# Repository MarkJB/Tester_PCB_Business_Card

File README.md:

# Tester PCB Business Card

A PCB Business Card designed by a tester, for testers (QA Engineers)

I've always liked the PCB business cards I've seen people design. They often have an interesting story about the why and the how, and sometimes even lead to a job offer as a result!

> Note: For any recruiters or prospective employers who end up here, I'm a software tester specializing in WebUI test automation. Electronics and hardware is a hobby (and occasionally a freelance gig in the Creative Technologist/Arts and Technology space)

I wanted to give it a go but couldn't think of anything compelling that was related to my primary industry (QA, Software Testing & Test Automation). Then I saw a recent [pong example on Hackaday](https://hackaday.com/2025/08/13/pcb-business-card-plays-pong-attracts-employer/) which made me wonder whether the author had done much testing, and that sparked the idea of creating a PCB business card all about testing.

There are 5 'test cases'\*, each one designed to be a little bit harder than the previous one and to focus on a different class of test. The hardware is somewhat limited, so how well each of the tests achieves its intended goal or how true it is to its test type is open for debate and I welcome feedback from actual testers!

The idea is that a tester should be able to look at the test case description, its test type and, given the available inputs and output, figure out how to get the tests to pass, treating it as a sort of black-box exploratory test session. Think of it as a fidget toy for tester.

That all said, I've not yet had any feedback from any testers so I don't know if its too easy or too hard. If you want to cheat, dig into this repo and you'll find the test case BDD scenarios and solutions (which I have deliberately not linked from any of the main READMEs), or as an alternative you can read the code (either the main firmware or the simulator should provide a white-box experience).

\* I use the term "test cases" to refer to the tests that the hardware is presenting to the end user to 'execute', but in some places I have also created actual tests for the code as well (like the Playwright tests for the simulator).

> Note: There may be minor differences between the simulator and the actual hardware due to implementation details or I changed direction while working on the firmware and haven't gotten round to updating the simulator.

So here is Rev A:

This is based on the CH32V003F4U6. A 27¢ micro controller with a one-wire programmer that costs less than $8. I had no experience with this when I started this project, but cost was a big factor with the card. I'm aiming for sub $2 per unit so I can a) afford to get a handful made and b) give them away at conferences and networking events.

> Note: I added a slot for attaching to a lanyard as I intend to give these out at networking and conference events.

This repo includes:

# Hardware

The [schematic](./resources/schematic.pdf), PCB design, BoM and JLCPCB ready production files [Kicad 9 files here](./hardware/)

# Software

## Simulator

Simulator [README](./software/simulator)

The simulator is built, tested and (if successful) deployed to GitHub pages by a [GitHub Actions pipeline](https://github.com/MarkJB/Tester_PCB_Business_Card/actions)

You can play with the deployed simulator here: [Simulator Demo](https://markjb.github.io/Tester_PCB_Business_Card/)

## Firmware

Uses platformio and the ch32fun framework.

[Main firmware](./software/firmware/tester_runtime/): The main firmware containing tests, test case runner, LED control, button functions etc.

[Board check](./software/firmware/board_check/): Simple test firmware to confirm LEDs and buttons are connected and working. Mainly used for testing hand assembled prototype boards.

[LED Tune](./software/firmware/led_tune/): Simple firmware to allow manual tuning of resistor values. shouldn't need this again unless the LEDs are changed for ones that are significantly different.

# Licenses

Copyright Mark Benson 2025

The hardware is licensed under the CERN-OHL-S v2 license.
The software is licensed under the MIT license.

Usual disclaimer - No warranty implied or given for any use or outcome of any of the available materials, etc. 

This isn't a toy, it's not suitable for children. As it's not in a case, there is a risk of short circuiting the components and battery, resulting in damage or overheating, so do not put it in your pocket or bag or anywhere where metal objects could cause short circuit. Note: Battery should be inserted + side up. Incorrectly inserted battery will short out resulting in damage or overheating. Use at your own risk.

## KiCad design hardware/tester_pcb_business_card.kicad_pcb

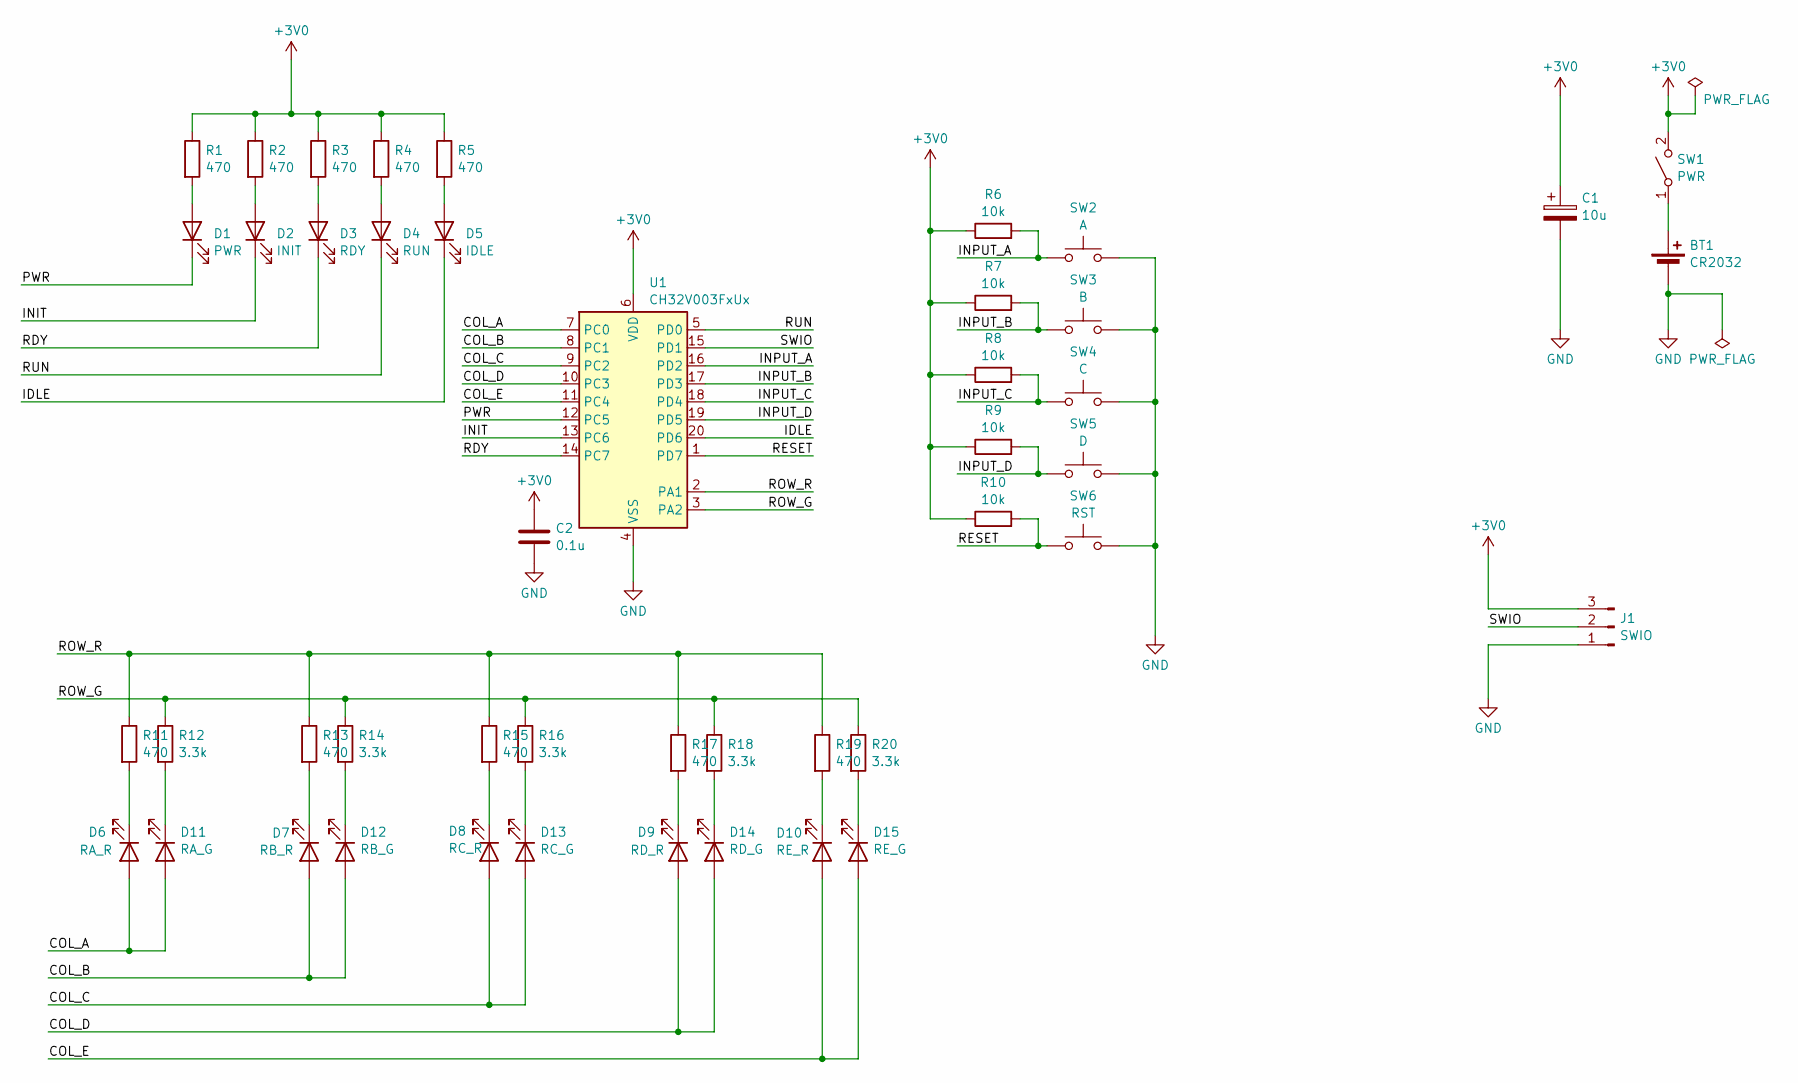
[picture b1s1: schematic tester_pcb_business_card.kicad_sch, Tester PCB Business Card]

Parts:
BT1: CR2032; MY-2032-12; LCSC C964833
C1: 10u; CP_EIA-3216-18_Kemet-A; LCSC C7171
C2: 0.1u; C_0805_2012Metric; LCSC C49678
D1: PWR; LED_0805_2012Metric; LCSC C84256
D2: INIT; LED_0805_2012Metric; LCSC C84256
D3: RDY; LED_0805_2012Metric; LCSC C84256
D4: RUN; LED_0805_2012Metric; LCSC C84256
D5: IDLE; LED_0805_2012Metric; LCSC C84256
D6: RA_R; LED_0805_2012Metric; LCSC C84256
D7: RB_R; LED_0805_2012Metric; LCSC C84256
D8: RC_R; LED_0805_2012Metric; LCSC C84256
D9: RD_R; LED_0805_2012Metric; LCSC C84256
D10: RE_R; LED_0805_2012Metric; LCSC C84256
D11: RA_G; LED_0805_2012Metric; LCSC C2297
D12: RB_G; LED_0805_2012Metric; LCSC C2297
D13: RC_G; LED_0805_2012Metric; LCSC C2297
D14: RD_G; LED_0805_2012Metric; LCSC C2297
D15: RE_G; LED_0805_2012Metric; LCSC C2297
J1: SWIO; PinHeader_1x03_P2.54mm_Vertical
R1, R2, R3, R4, R5, R11, R13, R15, R17, R19: 470; R_0603_1608Metric; LCSC C23179
R6, R7, R8, R9, R10: 10k; R_0603_1608Metric; LCSC C25804
R12, R14, R16, R18, R20: 3.3k; R_0603_1608Metric; LCSC C22978
SW1: PWR; SW_SPDT_Shouhan_MSK12C02; LCSC C431540
SW2: A; BTN_XUNPU_TS_1088-AR02016; LCSC C720477
SW3: B; BTN_XUNPU_TS_1088-AR02016; LCSC C720477
SW4: C; BTN_XUNPU_TS_1088-AR02016; LCSC C720477
SW5: D; BTN_XUNPU_TS_1088-AR02016; LCSC C720477
SW6: RST; BTN_XUNPU_TS_1088-AR02016; LCSC C720477
U1: CH32V003FxUx; QFN-20-1EP_3x3mm_P0.4mm_EP1.65x1.65mm; LCSC C5299908

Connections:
+3V0: C1.1, C2.1, J1.3, R1.1, R2.1, R3.1, R4.1, R5.1, R6.1, R7.1, R8.1, R9.1, R10.1, SW1.2 (B), U1.6 (VDD)
/COL_A: D6.2 (A), D11.2 (A), U1.7 (PC0)
/COL_B: D7.2 (A), D12.2 (A), U1.8 (PC1)
/COL_C: D8.2 (A), D13.2 (A), U1.9 (PC2)
/COL_D: D9.2 (A), D14.2 (A), U1.10 (PC3)
/COL_E: D10.2 (A), D15.2 (A), U1.11 (PC4)
/IDLE: D5.1 (K), U1.20 (PD6)
/INIT: D2.1 (K), U1.13 (PC6)
/INPUT_A: R6.2, SW2.1, U1.16 (PD2)
/INPUT_B: R7.2, SW3.1, U1.17 (PD3)
/INPUT_C: R8.2, SW4.1, U1.18 (PD4)
/INPUT_D: R9.2, SW5.1, U1.19 (PD5)
/PWR: D1.1 (K), U1.12 (PC5)
/RDY: D3.1 (K), U1.14 (PC7)
/RESET: R10.2, SW6.1, U1.1 (PD7)
/ROW_G: R12.1, R14.1, R16.1, R18.1, R20.1, U1.3 (PA2)
/ROW_R: R11.1, R13.1, R15.1, R17.1, R19.1, U1.2 (PA1)
/RUN: D4.1 (K), U1.5 (PD0)
/SWIO: J1.2, U1.15 (PD1)
GND: BT1.2 (-), C1.2, C2.2, J1.1, SW2.2, SW3.2, SW4.2, SW5.2, SW6.2, U1.4 (VSS), U1.21 (VSS)
unnamed: BT1.1 (+), SW1.1 (A)
unnamed: D1.2 (A), R1.2
unnamed: D2.2 (A), R2.2
unnamed: D3.2 (A), R3.2
unnamed: D4.2 (A), R4.2
unnamed: D5.2 (A), R5.2
unnamed: D6.1 (K), R11.2
unnamed: D7.1 (K), R13.2
unnamed: D8.1 (K), R15.2
unnamed: D9.1 (K), R17.2
unnamed: D10.1 (K), R19.2
unnamed: D11.1 (K), R12.2
unnamed: D12.1 (K), R14.2
unnamed: D13.1 (K), R16.2
unnamed: D14.1 (K), R18.2
unnamed: D15.1 (K), R20.2

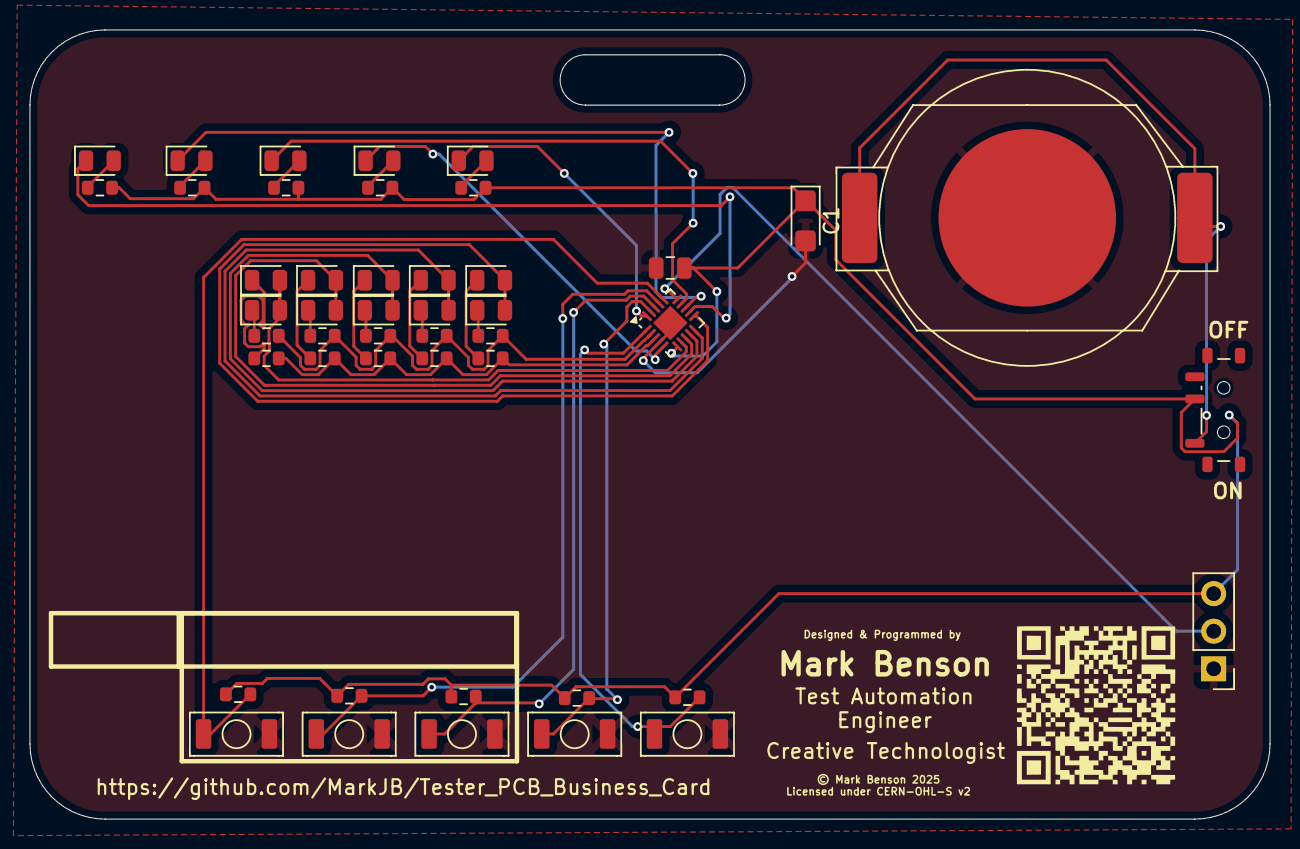
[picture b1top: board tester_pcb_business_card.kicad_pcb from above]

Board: 2 copper layers, 83.8 x 53.3 mm, 46 parts (0 on the bottom side), 36 nets.

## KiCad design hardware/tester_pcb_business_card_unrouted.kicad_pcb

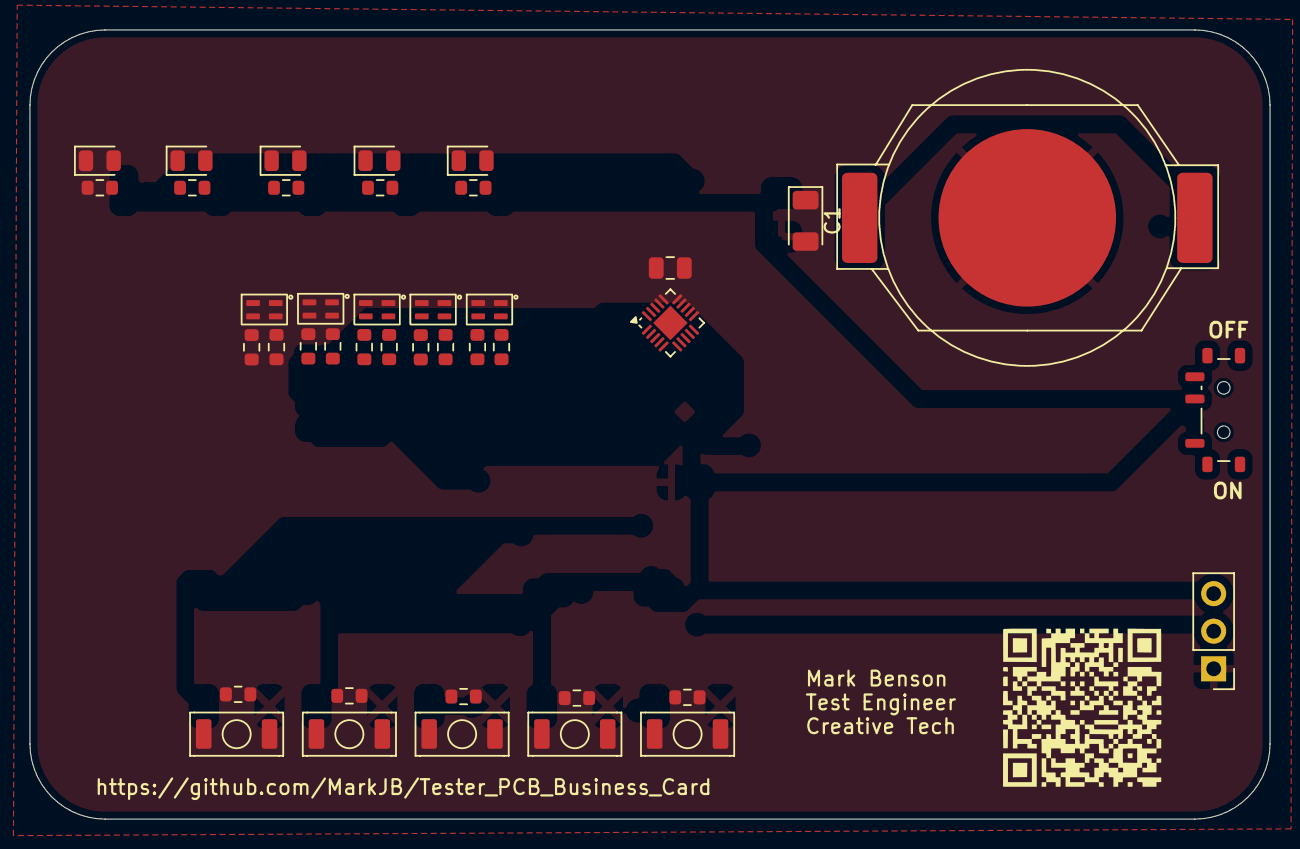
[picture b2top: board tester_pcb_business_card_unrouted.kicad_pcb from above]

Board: 2 copper layers, 83.8 x 53.3 mm, 41 parts (0 on the bottom side), 36 nets, no tracks yet.

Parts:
BT1: CR2032; MY-2032-12
C1: 10u; D_1206_3216Metric
C2: 0.1u; C_0805_2012Metric
D1: PWR; LED_0805_2012Metric
D2: INIT; LED_0805_2012Metric
D3: RDY; LED_0805_2012Metric
D4: RUN; LED_0805_2012Metric
D5: IDLE; LED_0805_2012Metric
D6: C; SML-522
D7: A; SML-522
D8: B; SML-522
D9: E; SML-522
D10: D; SML-522
J1: SWIO; PinHeader_1x03_P2.54mm_Vertical
R1, R2, R3, R4, R5, R11, R13, R15, R17, R19: 220; R_0603_1608Metric
R6, R7, R8, R9, R10: 10k; R_0603_1608Metric
R12, R14, R16, R18, R20: 100; R_0603_1608Metric
SW1: PWR; SW_SPDT_Shouhan_MSK12C02
SW2: A; BTN_XUNPU_TS_1088-AR02016
SW3: B; BTN_XUNPU_TS_1088-AR02016
SW4: C; BTN_XUNPU_TS_1088-AR02016
SW5: D; BTN_XUNPU_TS_1088-AR02016
SW6: RST; BTN_XUNPU_TS_1088-AR02016
U1: CH32V003FxUx; QFN-20-1EP_3x3mm_P0.4mm_EP1.65x1.65mm

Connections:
+3V0: C1.1, C2.1, J1.3, R1.1, R2.1, R3.1, R4.1, R5.1, R6.1, R7.1, R8.1, R9.1, R10.1, SW1.2 (B), U1.6 (VDD)
/COL_G: R12.1, R13.1, R15.1, R17.1, R19.1, U1.3 (PA2)
/COL_R: R11.1, R14.1, R16.1, R18.1, R20.1, U1.2 (PA1)
/IDLE: D5.2 (A), U1.20 (PD6)
/INIT: D2.2 (A), U1.13 (PC6)
/INPUT_A: R6.2, SW2.1, U1.16 (PD2)
/INPUT_B: R7.2, SW3.1, U1.17 (PD3)
/INPUT_C: R8.2, SW4.1, U1.18 (PD4)
/INPUT_D: R9.2, SW5.1, U1.19 (PD5)
/PWR: D1.2 (A), U1.12 (PC5)
/RDY: D3.2 (A), U1.14 (PC7)
/RESET: R10.2, SW6.1, U1.1 (PD7)
/ROW_A: D7.1 (A1), D7.3 (A2), U1.7 (PC0)
/ROW_B: D8.1 (A1), D8.3 (A2), U1.8 (PC1)
/ROW_C: D6.1 (A1), D6.3 (A2), U1.9 (PC2)
/ROW_D: D10.1 (A1), D10.3 (A2), U1.10 (PC3)
/ROW_E: D9.1 (A1), D9.3 (A2), U1.11 (PC4)
/RUN: D4.2 (A), U1.5 (PD0)
/SWIO: J1.2, U1.15 (PD1)
GND: BT1.2 (-), C1.2, C2.2, J1.1, SW2.2, SW3.2, SW4.2, SW5.2, SW6.2, U1.4 (VSS), U1.21 (VSS)
unnamed: BT1.1 (+), SW1.1 (A)
unnamed: D1.1 (K), R1.2
unnamed: D2.1 (K), R2.2
unnamed: D3.1 (K), R3.2
unnamed: D4.1 (K), R4.2
unnamed: D5.1 (K), R5.2
unnamed: D6.2 (K1), R15.2
unnamed: D6.4 (K2), R16.2
unnamed: D7.2 (K1), R11.2
unnamed: D7.4 (K2), R12.2
unnamed: D8.2 (K1), R13.2
unnamed: D8.4 (K2), R14.2
unnamed: D9.2 (K1), R19.2
unnamed: D9.4 (K2), R20.2
unnamed: D10.2 (K1), R17.2
unnamed: D10.4 (K2), R18.2

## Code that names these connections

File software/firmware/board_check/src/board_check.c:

#include "ch32fun.h"
#include <stdio.h>
#include <stdbool.h>

// Status Pins
#define PIN_PWR   PC5
#define PIN_INIT  PC6
#define PIN_RDY   PC7
#define PIN_RUN   PD0
#define PIN_IDLE  PD6

// Test Case Columns (TC1–TC5)
#define PIN_COL_A PC0
#define PIN_COL_B PC1
#define PIN_COL_C PC2
#define PIN_COL_D PC3
#define PIN_COL_E PC4

// Test Case Rows
#define PIN_ROW_R PA1  // Red (fail)
#define PIN_ROW_G PA2  // Green (pass)

// Input buttons
#define PIN_INPUT_A  PD2
#define PIN_INPUT_B  PD3
#define PIN_INPUT_C  PD4
#define PIN_INPUT_D  PD5

// Reset button is connected to NRST pin PD7 which should reset the MCU when pressed.
// This is a a hardware feature and does not require configuration.

const uint8_t statusLEDs[] = { PIN_INIT, PIN_RDY, PIN_RUN, PIN_IDLE };
const uint8_t cols[] = { PIN_COL_A, PIN_COL_B, PIN_COL_C, PIN_COL_D, PIN_COL_E };
const uint8_t inputPins[] = { PIN_INPUT_A, PIN_INPUT_B, PIN_INPUT_C, PIN_INPUT_D };
const uint8_t inputCols[] = { PIN_COL_A, PIN_COL_B, PIN_COL_C, PIN_COL_D }; // TC1–TC4
typedef enum {
    MODE_DEMO,
    MODE_INPUT
} BoardMode;

BoardMode currentMode = MODE_DEMO;
void runInputMode(void);

void setupPins() {
    funGpioInitAll();

    // Status LEDs
    funPinMode(PIN_PWR, GPIO_Speed_10MHz | GPIO_CNF_OUT_PP);
    funDigitalWrite(PIN_PWR, FUN_LOW); // Turn PWR ON immediately

    for (int i = 0; i < 4; i++) {
        funPinMode(statusLEDs[i], GPIO_Speed_10MHz | GPIO_CNF_OUT_PP);
        funDigitalWrite(statusLEDs[i], FUN_HIGH); // Ensure all status LEDs start OFF
    }

    // Test Case LEDs
    for (int i = 0; i < 5; i++) {
        funPinMode(cols[i], GPIO_Speed_10MHz | GPIO_CNF_OUT_PP);
        funDigitalWrite(cols[i], FUN_LOW); // Start all columns LOW
    }

    funPinMode(PIN_ROW_R, GPIO_Speed_10MHz | GPIO_CNF_OUT_PP);
    funPinMode(PIN_ROW_G, GPIO_Speed_10MHz | GPIO_CNF_OUT_PP);
    funDigitalWrite(PIN_ROW_R, FUN_HIGH); // Start rows OFF
    funDigitalWrite(PIN_ROW_G, FUN_HIGH);

    for (int i = 0; i < 4; i++) {
    funPinMode(inputPins[i], GPIO_CNF_IN_PUPD);
    funDigitalWrite(inputPins[i], FUN_HIGH); // enable pull‑up
}

}

bool isAnyButtonPressed() {
    for (int i = 0; i < 4; i++) {
        if (funDigitalRead(inputPins[i]) == FUN_LOW) {
            return true;
        }
    }
    return false;
}

void delayWithInputCheck(uint16_t ms) {
    uint16_t step = 5;
    for (uint16_t i = 0; i < ms; i += step) {
        if (isAnyButtonPressed()) {
            currentMode = MODE_INPUT;
            runInputMode(); // never returns
        }
        Delay_Ms(step);
    }
}

void blinkStatusSequence() {
    funDigitalWrite(PIN_PWR, FUN_LOW); // PWR stays on

    for (int i = 0; i < 4; i++) {
        funDigitalWrite(statusLEDs[i], FUN_LOW);
        delayWithInputCheck(200); // or delayWithInputCheck(100)
        funDigitalWrite(statusLEDs[i], FUN_HIGH);
        delayWithInputCheck(200); // or delayWithInputCheck(100)
    }
}

void scanTestCases() {
    for (int i = 0; i < 5; i++) {
        for (int j = 0; j < 5; j++) funDigitalWrite(cols[j], FUN_LOW);
        funDigitalWrite(PIN_ROW_G, FUN_HIGH);
        funDigitalWrite(PIN_ROW_R, FUN_HIGH);

        funDigitalWrite(cols[i], FUN_HIGH);
        funDigitalWrite(PIN_ROW_G, FUN_LOW);
        delayWithInputCheck(200); // or delayWithInputCheck(100)

        funDigitalWrite(PIN_ROW_G, FUN_HIGH);
        funDigitalWrite(PIN_ROW_R, FUN_LOW);
        delayWithInputCheck(200); // or delayWithInputCheck(100)

        funDigitalWrite(cols[i], FUN_LOW);
        funDigitalWrite(PIN_ROW_R, FUN_HIGH);
    }
}

void runInputMode() {
    // Turn off all LEDs except PWR
    for (int i = 0; i < 4; i++) funDigitalWrite(statusLEDs[i], FUN_HIGH);
    for (int i = 0; i < 5; i++) funDigitalWrite(cols[i], FUN_LOW);
    funDigitalWrite(PIN_ROW_R, FUN_HIGH);
    funDigitalWrite(PIN_ROW_G, FUN_HIGH);

    while (1) {
        bool anyPressed = false;

        for (int i = 0; i < 4; i++) {
            if (funDigitalRead(inputPins[i]) == FUN_LOW) {
                funDigitalWrite(inputCols[i], FUN_HIGH);
                anyPressed = true;
            } else {
                funDigitalWrite(inputCols[i], FUN_LOW);
            }
        }

        funDigitalWrite(PIN_ROW_G, anyPressed ? FUN_LOW : FUN_HIGH);
        Delay_Ms(50); // Responsive polling
    }
}

int main() {
    SystemInit();
    setupPins();

    while (1) {
        if (currentMode == MODE_DEMO) {
            if (isAnyButtonPressed()) {
                currentMode = MODE_INPUT;
                runInputMode(); // never returns
            }

            blinkStatusSequence();
            scanTestCases();
            Delay_Ms(500);
        }
    }
}

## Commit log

2025-08-21 Create .gitignore
    Excludes for kicad
2025-08-21 PCB initial commit
2025-08-21 Renders of PCB
2025-08-21 Add the test design markdown rough draft
2025-08-21 Add some initial details to readme
2025-08-21 Updates to readme
2025-08-22 Initial commit for web based card simulator
2025-08-23 Add 'glow' effect to LEDs
2025-08-23 Add test case 2, test case 'runner' and a bit of clean up of LED helper functions and comments
2025-08-23 Add systemState and update status checks to use that
2025-08-23 Add test case 3 and fix system state on boot
2025-08-23 Add visual indication to show which test is in progress
    Code needs cleaning up as we now have to clear the state of the test case LEDs before showing the final result - this could be done in a helper function.
2025-08-24 Make test functions more test like and have test runner handle system state
2025-08-24 Add test case 4 and improve LED handling
2025-08-24 Add setup and teardown to test runner and make use of that in tests
    Hopefully this will make creating test case 5 a bit easier.
    It should also help to extract the system logic from the test cases. As this is a simulator built to test how the card will behave when running these tests, the boundary between system behaviour and 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
2025-08-24 Update the Gherkin for test case 5 based on some early play testing
2025-08-25 Add positive and negative playwright tests for test cases 1-4
    This is a first pass so locators and actions are duplicated right now.
    Also test cases must be run in order which I don't like, but the SUT is stateful and its 'tests' run one after the other, so the playwright tests must match that. The test groups can be run in any or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
2025-08-25 Convert playwright tests to page/flow object model pattern
2025-08-25 Update version of node used for actions
2025-08-25 Add a timeout when waiting for dev server to start SUT
2025-08-25 Use the right location for the test results
2025-08-25 Configure playwright html reporter
2025-08-25 Add a test and deploy to gh-pages workflow
    This should run the playwright tests against the built version of the simulator and if the tests pass, uploads it to the gh-pages for this repo
2025-08-25 Fix typo in workflow name
2025-08-25 Let vite preview run in background
2025-08-25 Ensure CI tests against the vite preview build port
2025-08-25 Add id-token write permissions to deployment workflow
2025-08-25 Add write pages permission to deployment
2025-08-25 Add a vite config to define base path
2025-08-25 Add link to deployed simulator and update readme on number of tests implemented
2025-08-25 First pass at modularizing main.js
2025-08-25 Second pass at modularization
    This commit breaks a few things
2025-08-25 3rd pass at modularization - fix introduced issues
    The copilot led refactor was interesting - it lost or threw away a bunch of code and either the separation showed up or introduced some issues around timeouts not being cleared.
2025-08-26 Add status LED tests and improve other tests
2025-08-29 Update test case 5 again
2025-08-29 Clean up test case 5
2025-08-29 Add test case 5
2025-08-29 Refactor code to support test case 5
    Clean up timeout handling code and visual cue control
2025-08-29 Add playwright test cases for testing TC5 on simulator
2025-08-29 Supress page model output unless in debug mode (set by environment variable)
2025-08-29 Add test cases for TC5
2025-08-31 Update LED resistor values after tuning
    LEDs were way too bright with chosen resistor values. Tuned so all LEDs are of a similar brightness and to reduce current draw.
2025-08-31 Fix test case LEDs rows and cols
    I had them labelled the wrong way round. Didn't affect anything but it was confusing when referring to schematic when writing code for the test case LEDs.
2025-08-31 Add firmware/utility for manually tuning LED resistors
    This powers on the power status LED, the TC1 pass and fail LEDs to allow manual tuning of resistor values
2025-08-31 Board check firmware
    Initial test firmware that powers on the PWR LED, then briefly turns on each status LED in turn, followed by the test case LEDs.
    This is intended to test that the board functions are working correctly.
    Currently only checks the LEDs. Button check still to be added.
2025-09-01 Add button checks
    System starts up. PWR LED turns on. Other status LEDs light one after the other, followed by test case LEDs. Pattern repeats until an input button is pressed. Then the system switches into button tes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
2025-09-01 Clean up redundant code
2025-09-02 Main firmware initial commit
    So far all this does is display a startup sequence. The RUN/IDLE LED flashing is handled by a timer and ISR.
2025-09-02 Scan test case LEDs
    Partially working - does not update when using Delay or waitTicks
    Added config for hardware debugging in platformio/vscode
2025-09-05 commit just to save the code at this stage
2025-09-05 Working ISR
    Note: After a couple of days trying to track down hard faults, turns out it was down to the type of interrupt used.
    From what I understand "WCH-Interrupt-fast" is expecting the ISR to be stack safe - that is to say, don't call anything that touches the stack (library calls, functions, variables etc). Added the con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
2025-09-07 Fix button input state config
2025-09-07 Fix input button config
2025-09-07 Basic test case runner
2025-09-07 Add TC1, TC2 & TC3
2025-09-07 Add TC4
2025-09-07 Differentiate between retry and warning state
2025-09-08 Add TC5
2025-09-08 PCBs for Ministry of Testing TestBash Brighton 2025
2025-09-12 Refactor code into logical modules
2025-09-12 TC5 working
2025-09-12 Add early exit for TC5
    If solution is correct, or all retries are exhausted, exit test early
2025-09-16 Make button press states easier to debug and tests less flaky
2025-09-16 Basic PoV PoC
2025-09-16 Use Status LEDs to avoid test case LED matrix timing issues
2025-09-19 Add 'MoT 2025' PoV message
    Eye catching led flashing mode
2025-09-19 Add a rough and ready demo mode
2025-09-19 Update READMEs
2025-09-19 Fix links
2025-09-19 Update readme adding a photo of the actual production board
2025-10-16 firmware: only allow demo mode when no tests are selected (currentTest == 0)
2025-10-16 Fix comment

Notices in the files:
hardware/tester_pcb_business_card.kicad_pcb:
© Mark Benson 2025
Licensed under CERN-OHL-S v2
© Mark Benson 2025 Licensed under CERN-OHL-S v2
